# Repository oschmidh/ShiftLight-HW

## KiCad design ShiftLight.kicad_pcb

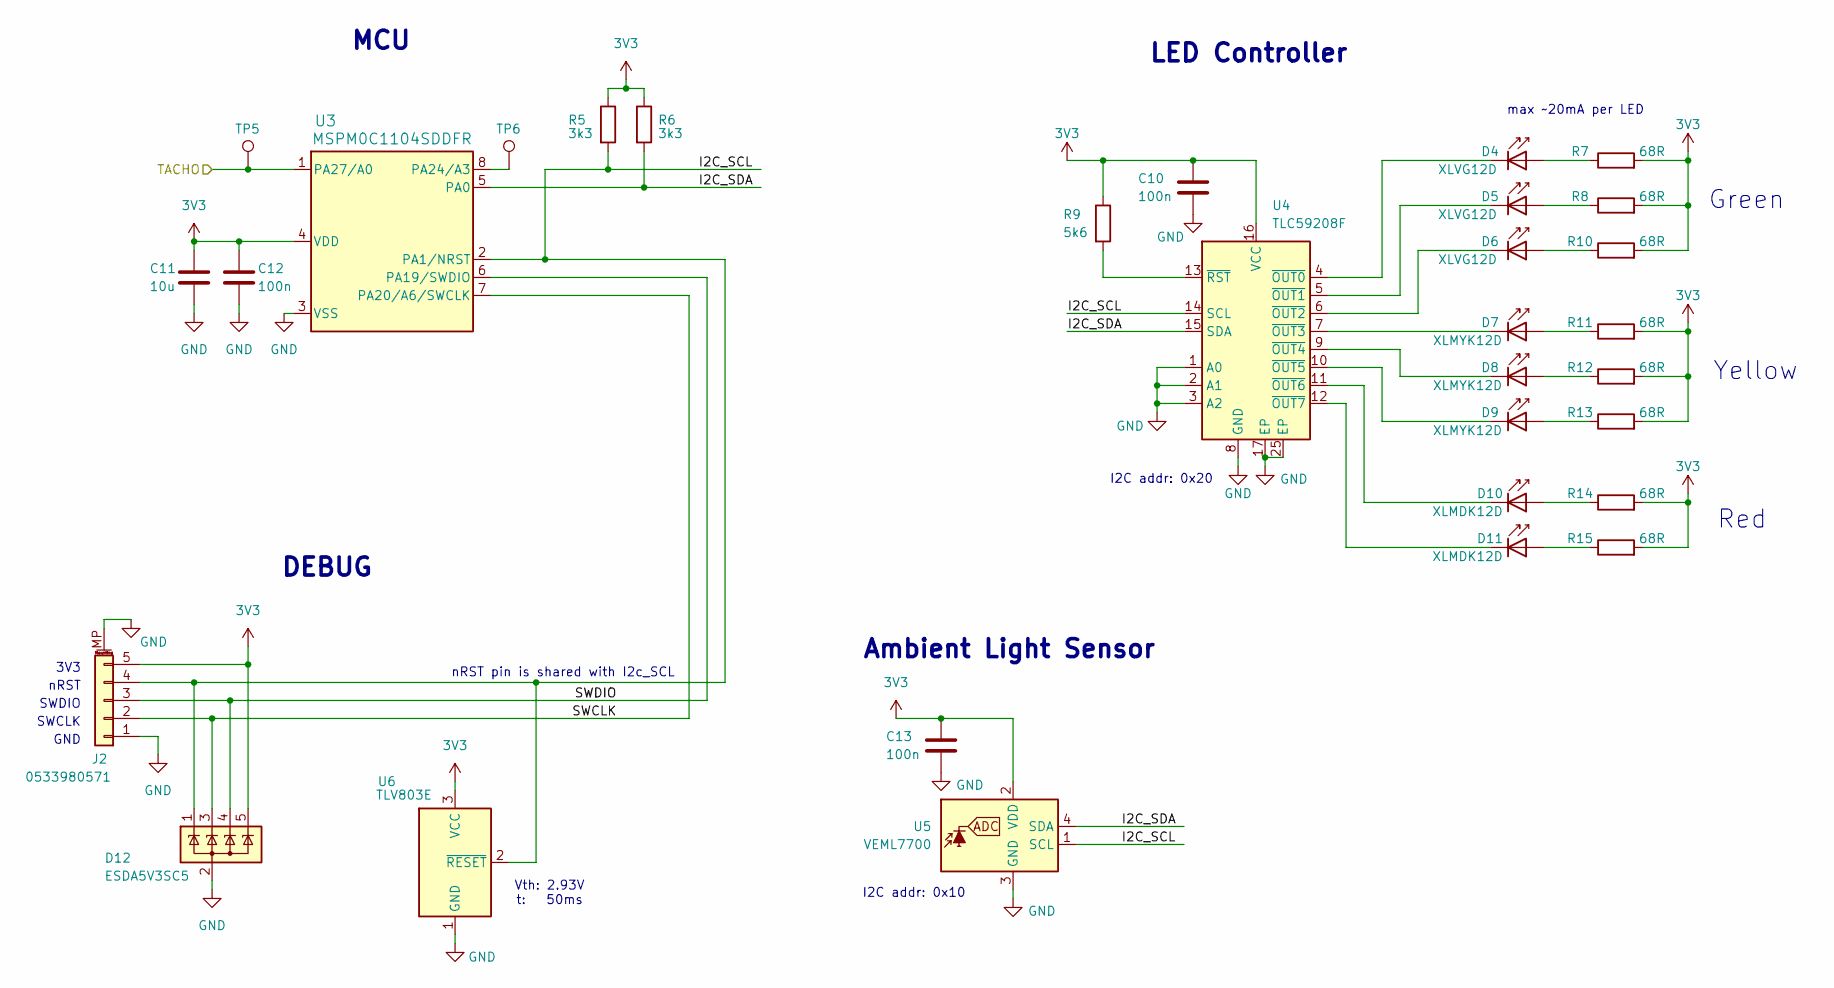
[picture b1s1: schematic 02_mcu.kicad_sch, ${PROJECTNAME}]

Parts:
C10, C12, C13: 100n; C_0402_1005Metric; MPN CL05B104KA5NNNC; DigiKey PN 1276-6720-1-ND
C11: 10u; C_1206_3216Metric; MPN CL31B106KAHNNNE; DigiKey PN 1276-1804-1-ND
D4, D5, D6: XLVG12D; LED_D5.0mm_IRGrey; MPN XLVG12D; DigiKey PN 1497-XLVG12D-ND
D7, D8, D9: XLMYK12D; LED_D5.0mm_IRGrey; MPN XLMYK12D; DigiKey PN XLMYK12D-ND
D10, D11: XLMDK12D; LED_D5.0mm_IRGrey; MPN XLMDK12D; DigiKey PN 1497-1354-ND
D12: ESDA5V3SC5; SOT-23-5; MPN ESDA5V3SC5; DigiKey PN 497-7746-1-ND
J2: 0533980571; Molex_PicoBlade_53398-0571_1x05-1MP_P1.25mm_Vertical; MPN 0533980571; DigiKey PN WM7609CT-ND
R5, R6: 3k3; R_0402_1005Metric; MPN RC0402FR-133K3L; DigiKey PN 13-RC0402FR-133K3LCT-ND
R7, R8, R10, R11, R12, R13, R14, R15: 68R; R_0402_1005Metric; MPN RC0402FR-0768RL; DigiKey PN 311-68.0LRCT-ND
R9: 5k6; R_0402_1005Metric; MPN RC0402FR-075K6L; DigiKey PN 311-5.6KLRCT-ND
TP5, TP6: TestPoint_Pad_D1.0mm
U3: MSPM0C1104SDDFR; SOT-23-8; MPN MSPM0C1104SDDFR; DigiKey PN 296-MSPM0C1104SDDFRCT-ND
U4: TLC59208F; Texas_RGY_R-PVQFN-N16_EP2.05x2.55mm_ThermalVias; MPN TLC59208FIRGYR; DigiKey PN 296-36989-1-ND
U5: VEML7700; Vishay_VEML7700; MPN VEML7700-TR; DigiKey PN VEML7700CT-ND
U6: TLV803E; SOT-23; MPN TLV803ED29DBZR; DigiKey PN 296-TLV803ED29DBZRCT-ND

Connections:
3V3: C10.1, C11.2, C12.1, C13.1, D12.5 (K), J2.5, R5.1, R6.1, R7.2, R8.2, R9.1, R10.2, R11.2, R12.2, R13.2, R14.2, R15.2, U3.4 (VDD), U4.16 (VCC), U5.2 (VDD), U6.3 (VCC); also elsewhere on the board
/01_Input/TACHO: TP5.1, U3.1 (PA27/A0); also elsewhere on the board
/02_MCU/I2C_SCL: D12.1 (K), J2.4, R5.2, U3.2 (PA1/NRST), U4.14 (SCL), U5.1 (SCL), U6.2 (~RESET)
/02_MCU/I2C_SDA: R6.2, U3.5 (PA0), U4.15 (SDA), U5.4 (SDA)
/02_MCU/SWCLK: D12.3 (K), J2.2, U3.7 (PA20/A6/SWCLK)
/02_MCU/SWDIO: D12.4 (K), J2.3, U3.6 (PA19/SWDIO)
GND: C10.2, C11.1, C12.2, C13.2, D12.2 (A), J2.1, J2.MP (MountPin), U3.3 (VSS), U4.1 (A0), U4.2 (A1), U4.3 (A2), U4.8 (GND), U4.17 (EP), U4.25 (EP), U5.3 (GND), U6.1 (GND); also elsewhere on the board
unnamed: D4.2 (A), R7.1
unnamed: D4.1 (K), U4.4 (~OUT0)
unnamed: D5.2 (A), R8.1
unnamed: D5.1 (K), U4.5 (~OUT1)
unnamed: D6.2 (A), R10.1
unnamed: D6.1 (K), U4.6 (~OUT2)
unnamed: D7.2 (A), R11.1
unnamed: D7.1 (K), U4.7 (~OUT3)
unnamed: D8.2 (A), R12.1
unnamed: D8.1 (K), U4.9 (~OUT4)
unnamed: D9.2 (A), R13.1
unnamed: D9.1 (K), U4.10 (~OUT5)
unnamed: D10.2 (A), R14.1
unnamed: D10.1 (K), U4.11 (~OUT6)
unnamed: D11.2 (A), R15.1
unnamed: D11.1 (K), U4.12 (~OUT7)
unnamed: TP6.1, U3.8 (PA24/A3)
unnamed: R9.2, U4.13 (~RST)

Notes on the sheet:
I2C addr: 0x20
I2C addr: 0x10
Green
Red
max ~20mA per LED
Ambient Light Sensor
nRST
MCU
SWCLK
3V3
nRST pin is shared with I2c_SCL
GND
Yellow
Vth: 2.93V t: 50ms
LED Controller
SWDIO
DEBUG

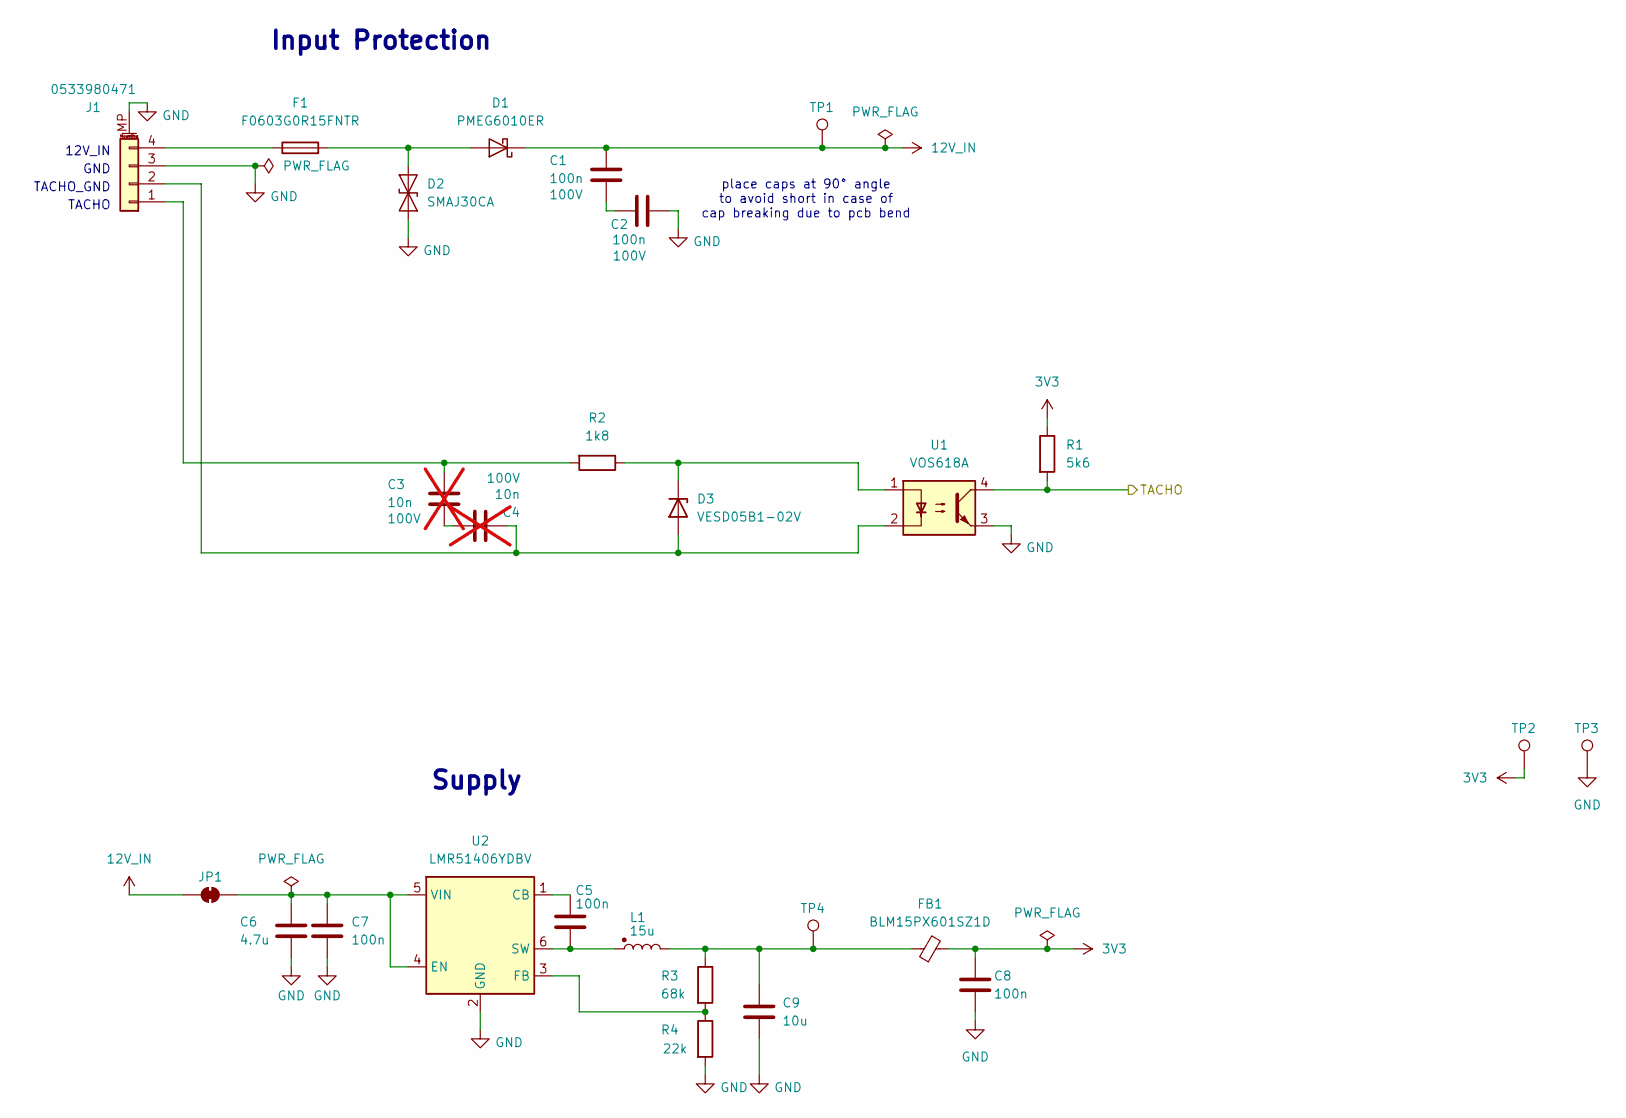
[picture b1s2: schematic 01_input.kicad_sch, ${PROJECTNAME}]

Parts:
C1, C2: 100n; C_0805_2012Metric; Voltage 100V; MPN CL21B104KCFWPNE; DigiKey PN 1276-6733-1-ND
C3, C4: 10n; C_0402_1005Metric; Voltage 100V; MPN HMK105B7103KVHFE; DigiKey PN 587-HMK105B7103KVHFECT-ND; not fitted
C5, C7, C8: 100n; C_0402_1005Metric; MPN CL05B104KA5NNNC; DigiKey PN 1276-6720-1-ND
C6: 4.7u; C_1206_3216Metric; MPN CL31B475KBHVPJE; DigiKey PN 1276-CL31B475KBHVPJECT-ND
C9: 10u; C_1206_3216Metric; MPN CL31B106KAHNNNE; DigiKey PN 1276-1804-1-ND
D1: PMEG6010ER; Nexperia_CFP3_SOD-123W; MPN PMEG6010ER,115; DigiKey PN 1727-5846-1-ND
D2: SMAJ30CA; D_SMA; MPN SMAJ30CA; DigiKey PN SMAJ30CALFCT-ND
D3: VESD05B1-02V; D_SOD-523; MPN VESD05B1-02V-G3-08; DigiKey PN VESD05B1-02V-G3-08GICT-ND
F1: F0603G0R15FNTR; Fuse_0603_1608Metric; MPN F0603G0R15FNTR; Mouser No 581-F0603G0R15FNTR
FB1: BLM15PX601SZ1D; L_0402_1005Metric; MPN BLM15PX601SZ1D; DigiKey PN 490-16655-1-ND
J1: 0533980471; Molex_PicoBlade_53398-0471_1x04-1MP_P1.25mm_Vertical; MPN 0533980471; DigiKey PN WM7608CT-ND
JP1: SolderJumper-2_P1.3mm_Bridged_RoundedPad1.0x1.5mm
L1: 15u; L_TDK_VLS3015CX; MPN VLS3015CX-150M-H; DigiKey PN 445-VLS3015CX-150M-HCT-ND
R1: 5k6; R_0402_1005Metric; MPN RC0402FR-075K6L; DigiKey PN 311-5.6KLRCT-ND
R2: 1k8; R_0402_1005Metric; MPN RC0402FR-071K8L; DigiKey PN 311-1.80KLRCT-ND
R3: 68k; R_0402_1005Metric; MPN RC0402FR-0768KL; DigiKey PN 311-68.0KLRCT-ND
R4: 22k; R_0402_1005Metric; MPN RC0402FR-0722KL; DigiKey PN 311-22.0KLRCT-ND
TP1, TP2, TP3, TP4: TestPoint_Pad_D1.0mm
U1: VOS618A; SSOP-4_4.4x2.6mm_P1.27mm; MPN VOS618A-3X001T; DigiKey PN VOS618A-3X001TCT-ND
U2: LMR51406YDBV; SOT-23-6; MPN LMR51406YDBV; DigiKey PN 296-LMR51406YDBVRCT-ND

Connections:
3V3: C8.1, FB1.2, R1.1, TP2.1; also elsewhere on the board
12V_IN: C1.1, D1.1 (K), JP1.1 (A), TP1.1
/01_Input/TACHO: R1.2, U1.4; also elsewhere on the board
GND: C2.2, C6.2, C7.2, C8.2, C9.1, D2.1 (A1), J1.3, J1.MP (MountPin), R4.2, TP3.1, U1.3, U2.2 (GND); also elsewhere on the board
unnamed: C1.2, C2.1
unnamed: C3.2, C4.1
unnamed: C9.2, FB1.1, L1.2, R3.1, TP4.1
unnamed: D1.2 (A), D2.2 (A2), F1.2
unnamed: C4.2, D3.2 (A), J1.2, U1.2
unnamed: D3.1 (K), R2.1, U1.1
unnamed: C3.1, J1.1, R2.2
unnamed: F1.1, J1.4
unnamed: C6.1, C7.1, JP1.2 (B), U2.4 (EN), U2.5 (VIN)
unnamed: C5.1, U2.1 (CB)
unnamed: R3.2, R4.1, U2.3 (FB)
unnamed: C5.2, L1.1, U2.6 (SW)

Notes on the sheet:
TACHO
Input Protection
Supply
place caps at 90° angle to avoid short in case of cap breaking due to pcb bend
12V_IN
GND
TACHO_GND

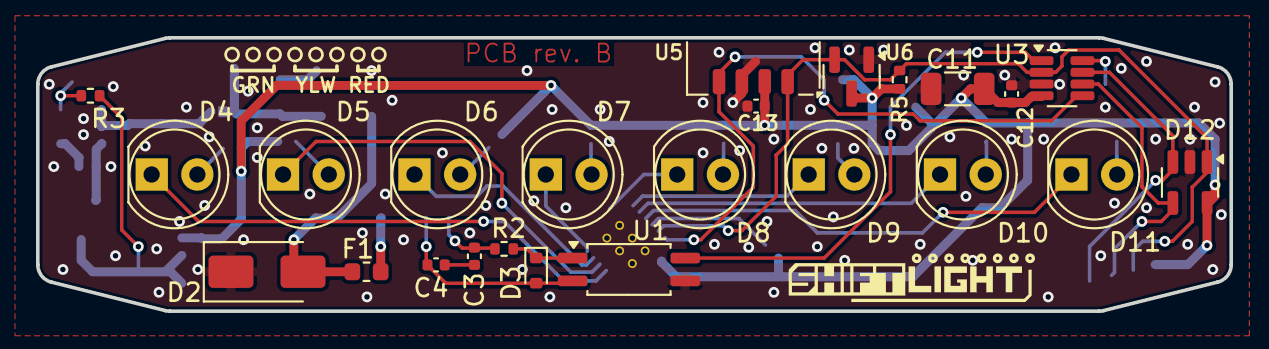
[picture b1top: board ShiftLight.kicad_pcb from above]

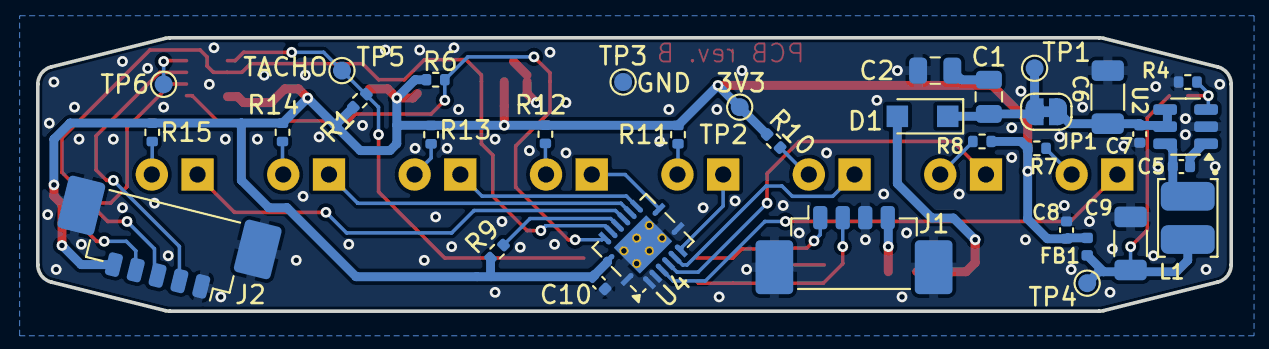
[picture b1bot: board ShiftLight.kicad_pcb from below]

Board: 2 copper layers, 66.3 x 15.2 mm, 58 parts (34 on the bottom side), 38 nets.

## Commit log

2025-05-03 Setup project
2025-07-08 Update schematic, make hierarchical
2025-07-09 Schematic: Update, annotate
2025-07-09 Layout: Import, start placement
2025-07-14 Schematic: Adjust pinouts for easier routing
2025-07-14 Layout: Initial component placement
2025-07-22 Ci: Add workflow to run DRC and export output files
2025-07-22 Fix file names
2025-07-22 fix for no tags
2025-07-22 also add outputs as artifacts
2025-07-22 fix env var expansion
2025-07-22 fix paths
2025-07-22 fix bom file ending, add rev to artifact name
2025-07-22 fix rev
2025-07-22 Add personal library
2025-07-22 fix library name
2025-07-22 Layout: Adjust design rules
2025-07-22 Schematic: Fix different 3V3 netnames, optimize pinouts
2025-07-22 Layout: Finish routing, start silkscreen cleanup
2025-07-24 Layout: Cleanup silkscreen and assembly drawing
2025-07-24 Ci: improvements
    - Fail action run on ERC or DRC error
    - Only upload ERC or DRC if they failed
2025-07-24 always run erc and drc
2025-07-24 fix version, test copy config
2025-07-24 remove src subfolder
2025-07-24 fix erc, upload single file
2025-07-24 fix error
2025-07-24 cleanup
2025-07-24 Ci: Improve action script
    - Fail action run on ERC or DRC error
    - Only upload ERC or DRC if they failed
2025-07-24 Layout: Update footprints to fix DRC errors
2025-07-24 Schematic: Add PWR_FLAGs to fix ERC errors
2025-07-24 Schematic: Remove nRST net label to avoid ERC warning
2025-07-24 Layout: Minor improvements
2025-07-24 Adjust rules for via sizes
    Using smaller vias would significantly increase the price (on JLCPCB)
2025-07-24 Ci: Generate gerber files
2025-07-24 Ci: Fill title header in generated schematic
2025-07-24 Ci: Change BOM delimiter
2025-07-24 Ci: Use protel file extension for Gerberfiles
    This is preferred by JLCPCB
2025-07-24 Ci: Generate Drill files
2025-07-24 Ci: Cleanup file
2025-07-24 Schematic: Remove Testpoints from BOM
2025-07-25 Add MPN and DigiKey PN to all components
2025-07-25 Adjust BOM for ordering at DigiKey
2025-07-30 Layout: Minor cleanup
2025-07-30 Ci: Also run action on tag push
2025-11-02 Schematic: Update comments for I2c addresses of devices
    Fix incorrect address for LED driver and add address of ambient light
    sensor.
2025-11-02 Fix swapped SCL and SDA pins for VEML7700
2025-11-02 Layout: Increment revision to B
2025-11-02 Fix footprint of tlv803e
2025-11-02 cleanup silkscreen
2025-11-02 Fix wrong footprint for TLV803E
